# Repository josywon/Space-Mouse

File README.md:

# Space-Mouse
6DoF Space Mouse
Hardware folder holds CAD files and BOM of any hardware used
Electrical includes PCB and BOM of electrical materials
Firmware will be connecting the mouse to the software

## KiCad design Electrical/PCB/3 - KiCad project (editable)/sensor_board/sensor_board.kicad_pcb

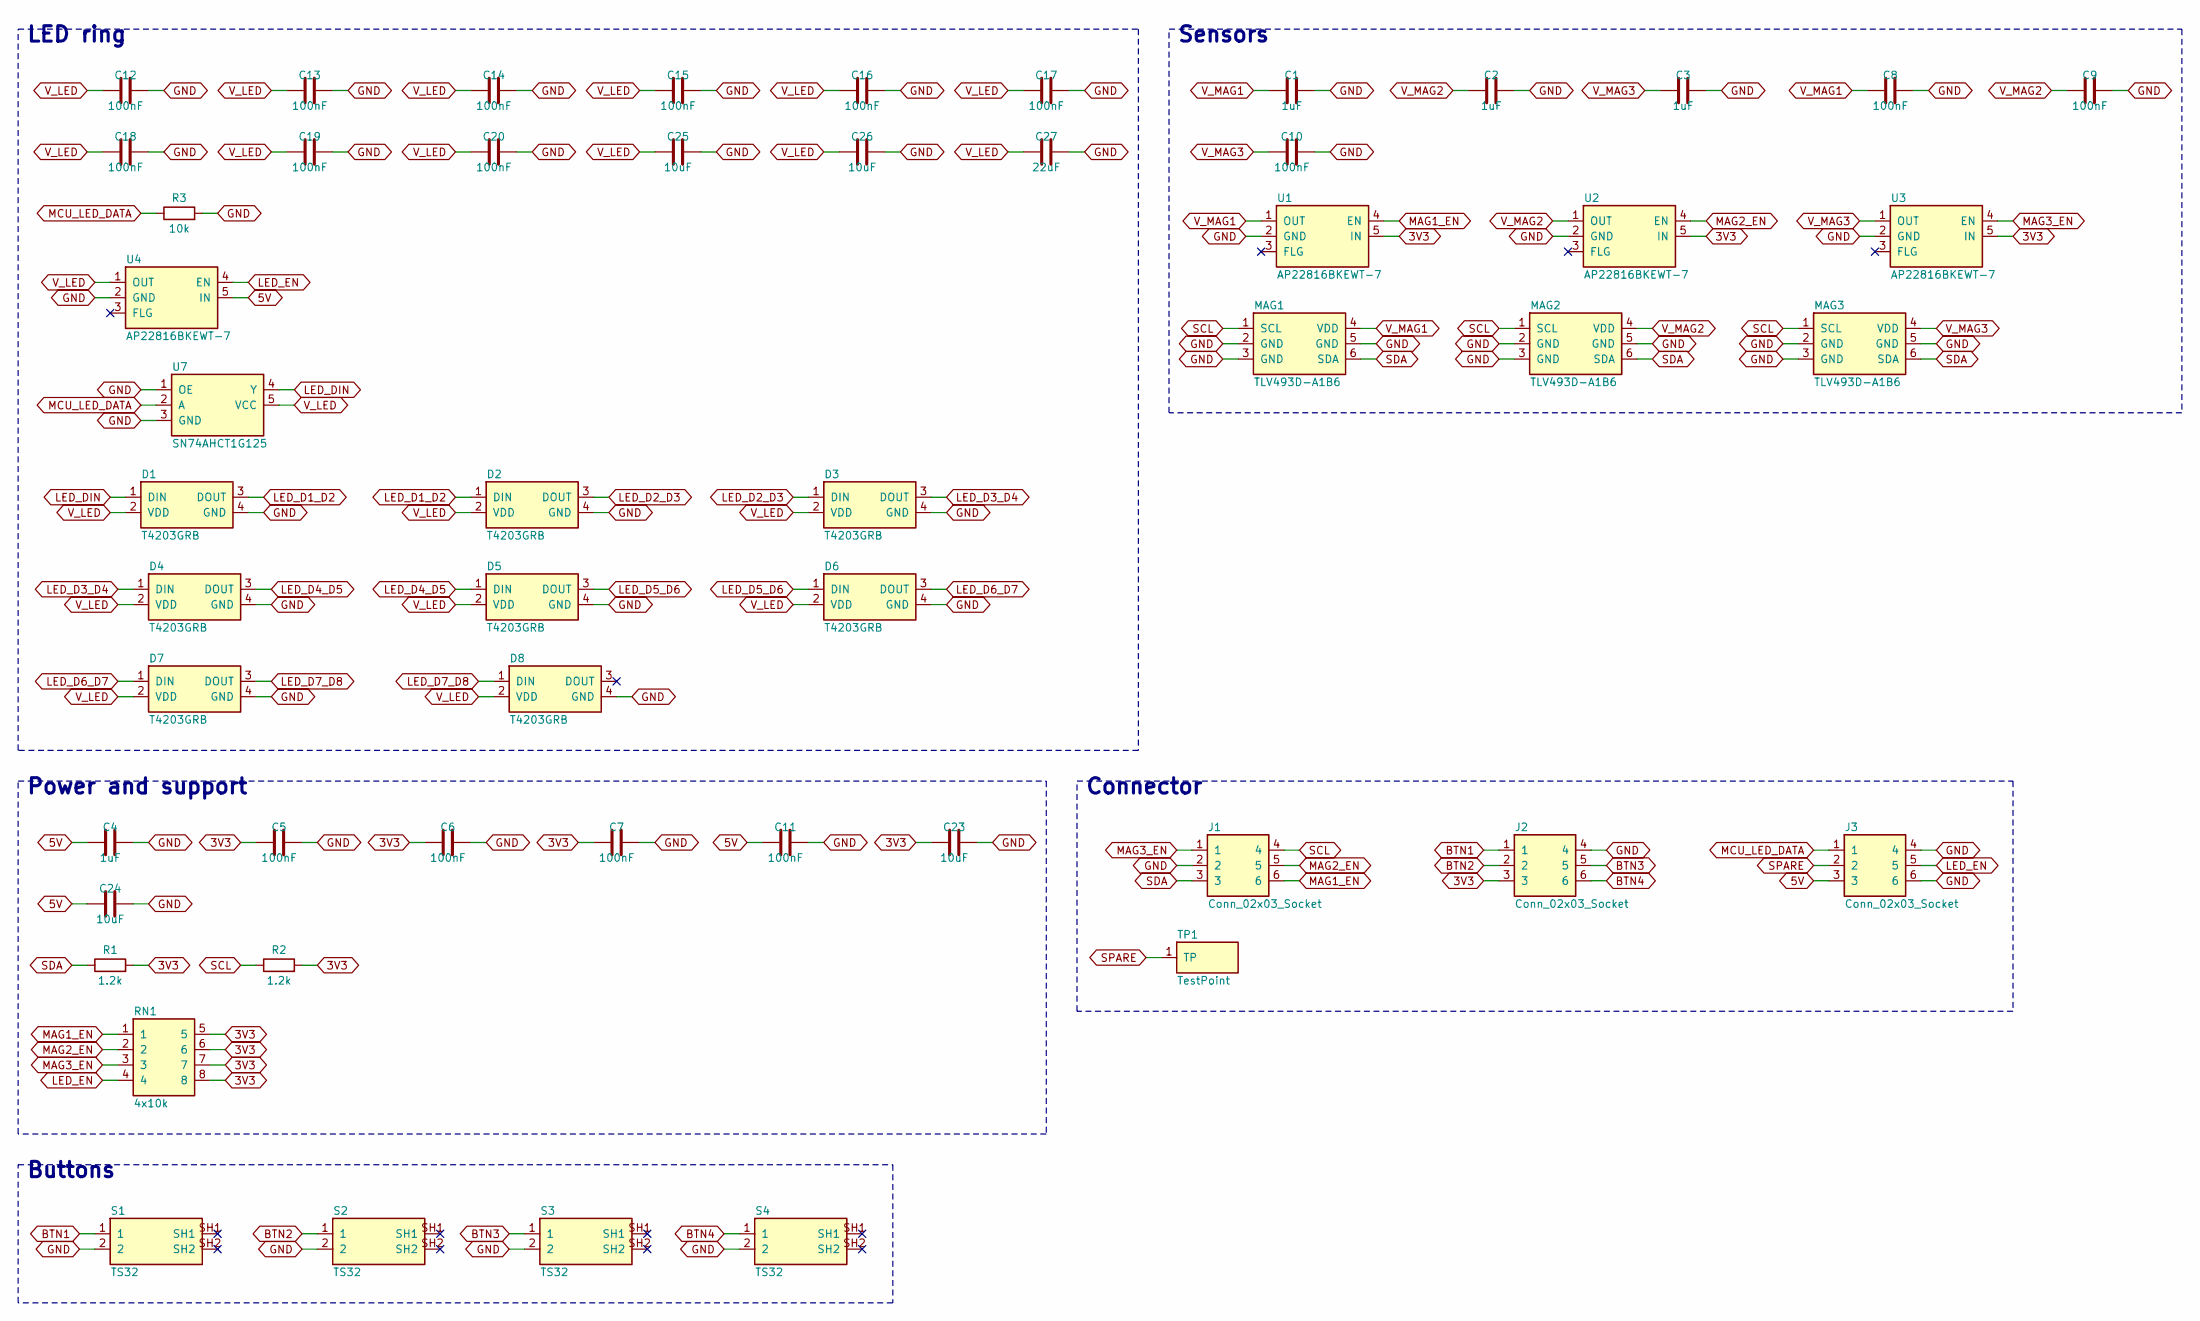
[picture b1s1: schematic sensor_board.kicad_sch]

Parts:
C1, C2, C3, C4: 1uF; C_1206_3216Metric
C5, C6, C7, C8, C9, C10, C11, C12, C13, C14, C15, C16, C17, C18, C19, C20: 100nF; C_0805_2012Metric
C23, C24, C25, C26: 10uF; C_0805_2012Metric
C27: 22uF; C_1206_3216Metric
D1, D2, D3, D4, D5, D6, D7, D8: T4203GRB; LED_T4203_SideView
J1, J2, J3: Conn_02x03_Socket; PinSocket_2x03_P2.00mm_Vertical
MAG1, MAG2, MAG3: TLV493D-A1B6; TSOP-6_1.65x3.05mm_P0.95mm
R1, R2: 1.2k; R_0805_2012Metric
R3: 10k; R_0805_2012Metric
RN1: 4x10k; R_Array_Convex_4x0603
S1, S2, S3, S4: TS32; SW_TS32_SideActuated
TP1: TestPoint; TestPoint_Pad_D1.5mm
U1, U2, U3, U4: AP22816BKEWT-7; TSOT-23-5
U7: SN74AHCT1G125; SOT-23-5

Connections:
3V3: C5.1, C6.1, C7.1, C23.1, J2.3, R1.2, R2.2, RN1.5, RN1.6, RN1.7, RN1.8, U1.5 (IN), U2.5 (IN), U3.5 (IN)
5V: C4.1, C11.1, C24.1, J3.3, U4.5 (IN)
BTN1: J2.1, S1.1
BTN2: J2.2, S2.1
BTN3: J2.5, S3.1
BTN4: J2.6, S4.1
GND: C1.2, C2.2, C3.2, C4.2, C5.2, C6.2, C7.2, C8.2, C9.2, C10.2, C11.2, C12.2, C13.2, C14.2, C15.2, C16.2, C17.2, C18.2, C19.2, C20.2, C23.2, C24.2, C25.2, C26.2, C27.2, D1.4 (GND), D2.4 (GND), D3.4 (GND), D4.4 (GND), D5.4 (GND), D6.4 (GND), D7.4 (GND), D8.4 (GND), J1.2, J2.4, J3.4, J3.6, MAG1.2 (GND), MAG1.3 (GND), MAG1.5 (GND), MAG2.2 (GND), MAG2.3 (GND), MAG2.5 (GND), MAG3.2 (GND), MAG3.3 (GND), MAG3.5 (GND), R3.2, S1.2, S2.2, S3.2, S4.2, U1.2 (GND), U2.2 (GND), U3.2 (GND), U4.2 (GND), U7.1 (OE), U7.3 (GND)
LED_D1_D2: D1.3 (DOUT), D2.1 (DIN)
LED_D2_D3: D2.3 (DOUT), D3.1 (DIN)
LED_D3_D4: D3.3 (DOUT), D4.1 (DIN)
LED_D4_D5: D4.3 (DOUT), D5.1 (DIN)
LED_D5_D6: D5.3 (DOUT), D6.1 (DIN)
LED_D6_D7: D6.3 (DOUT), D7.1 (DIN)
LED_D7_D8: D7.3 (DOUT), D8.1 (DIN)
LED_DIN: D1.1 (DIN), U7.4 (Y)
LED_EN: J3.5, RN1.4, U4.4 (EN)
MAG1_EN: J1.6, RN1.1, U1.4 (EN)
MAG2_EN: J1.5, RN1.2, U2.4 (EN)
MAG3_EN: J1.1, RN1.3, U3.4 (EN)
MCU_LED_DATA: J3.1, R3.1, U7.2 (A)
SCL: J1.4, MAG1.1 (SCL), MAG2.1 (SCL), MAG3.1 (SCL), R2.1
SDA: J1.3, MAG1.6 (SDA), MAG2.6 (SDA), MAG3.6 (SDA), R1.1
SPARE: J3.2, TP1.1
V_LED: C12.1, C13.1, C14.1, C15.1, C16.1, C17.1, C18.1, C19.1, C20.1, C25.1, C26.1, C27.1, D1.2 (VDD), D2.2 (VDD), D3.2 (VDD), D4.2 (VDD), D5.2 (VDD), D6.2 (VDD), D7.2 (VDD), D8.2 (VDD), U4.1 (OUT), U7.5 (VCC)
V_MAG1: C1.1, C8.1, MAG1.4 (VDD), U1.1 (OUT)
V_MAG2: C2.1, C9.1, MAG2.4 (VDD), U2.1 (OUT)
V_MAG3: C3.1, C10.1, MAG3.4 (VDD), U3.1 (OUT)

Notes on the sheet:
LED ring
Sensors
Power and support
Connector
Buttons

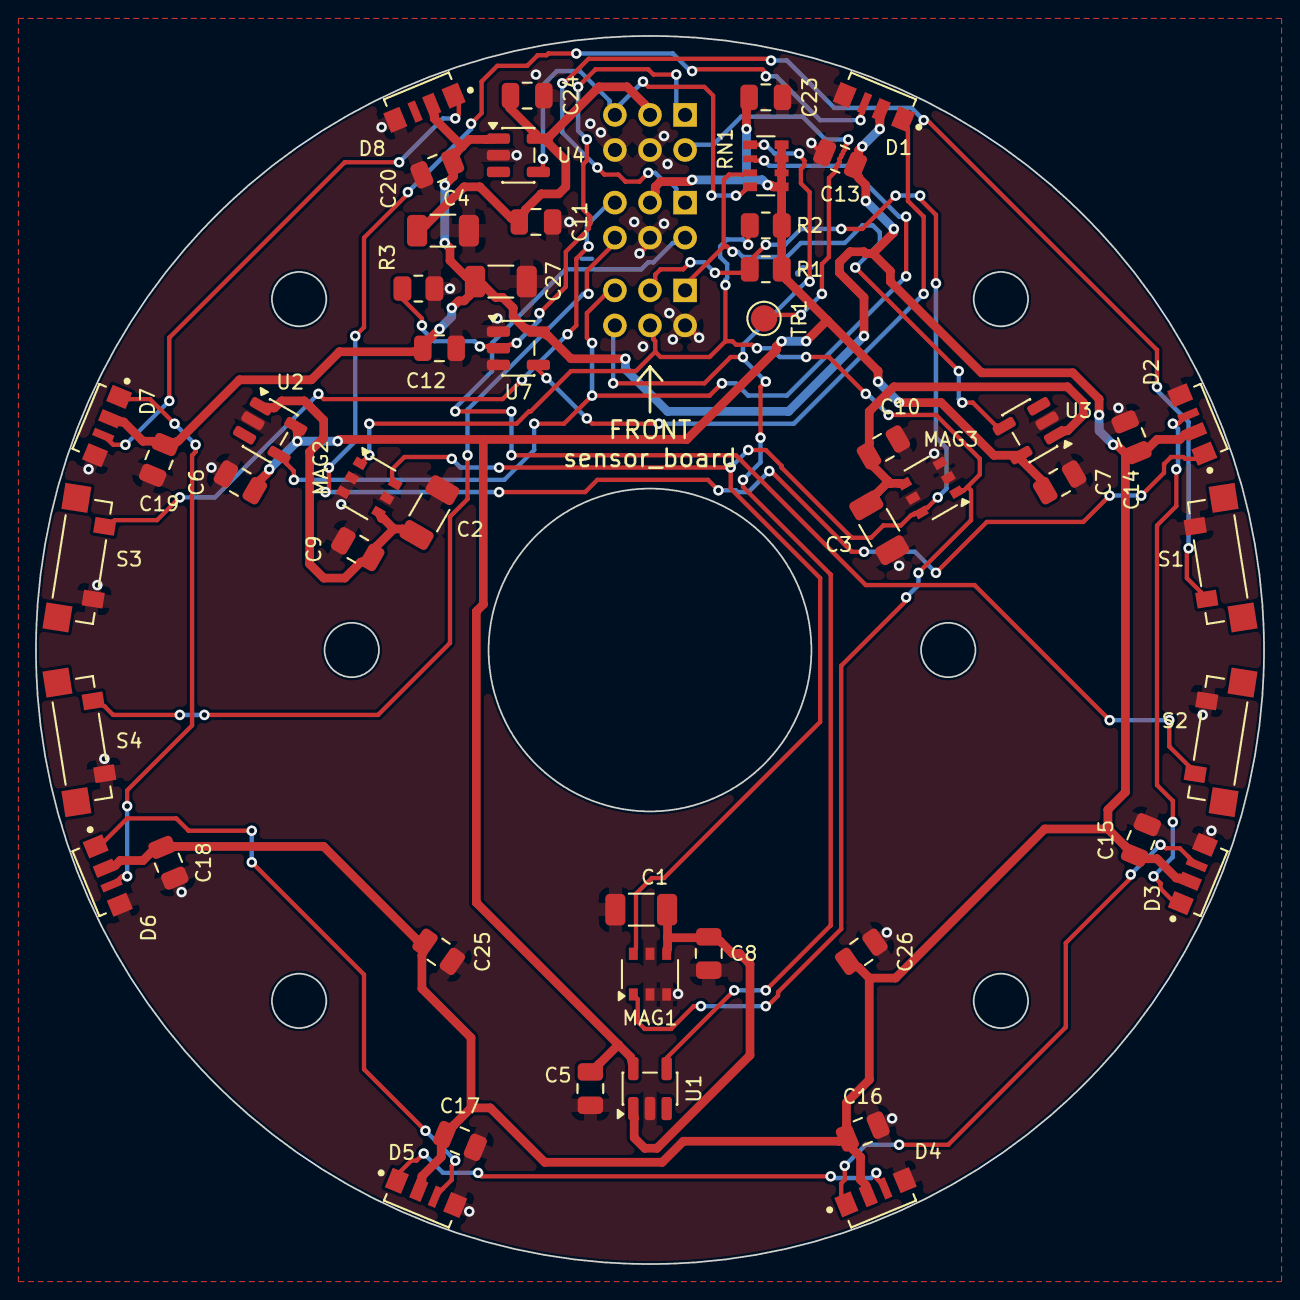
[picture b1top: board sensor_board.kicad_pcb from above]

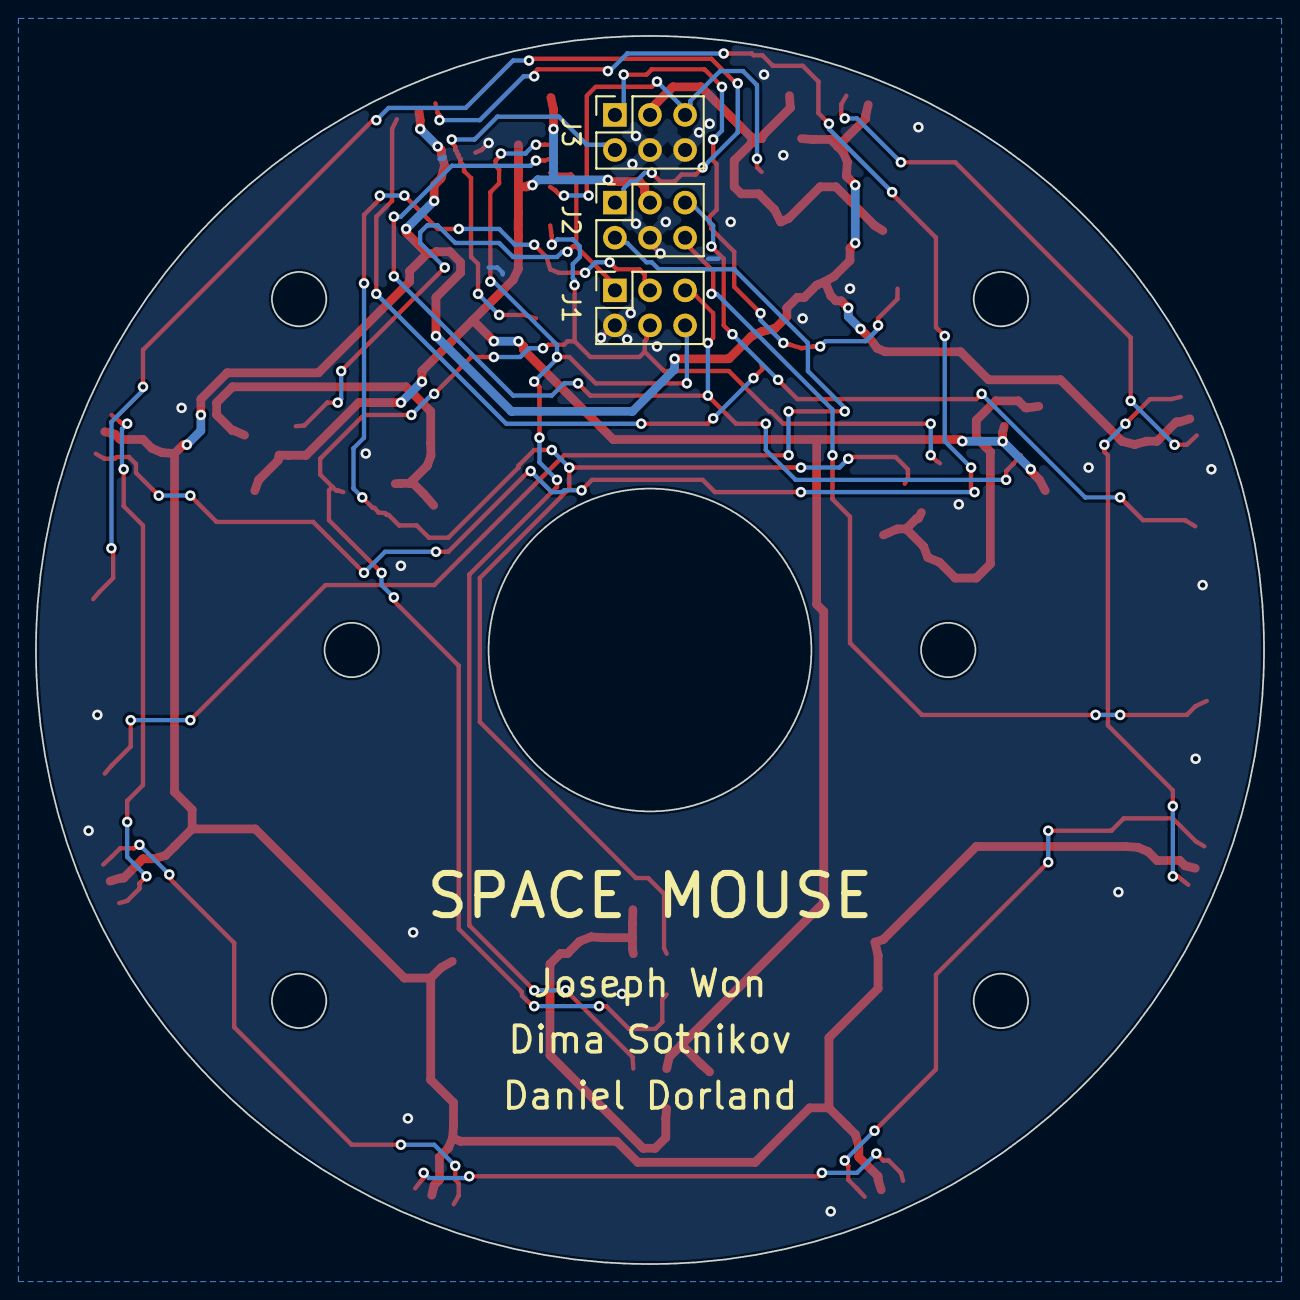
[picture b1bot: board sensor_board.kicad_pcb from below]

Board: 2 copper layers, 70.0 x 70.0 mm, 53 parts (3 on the bottom side), 27 nets.

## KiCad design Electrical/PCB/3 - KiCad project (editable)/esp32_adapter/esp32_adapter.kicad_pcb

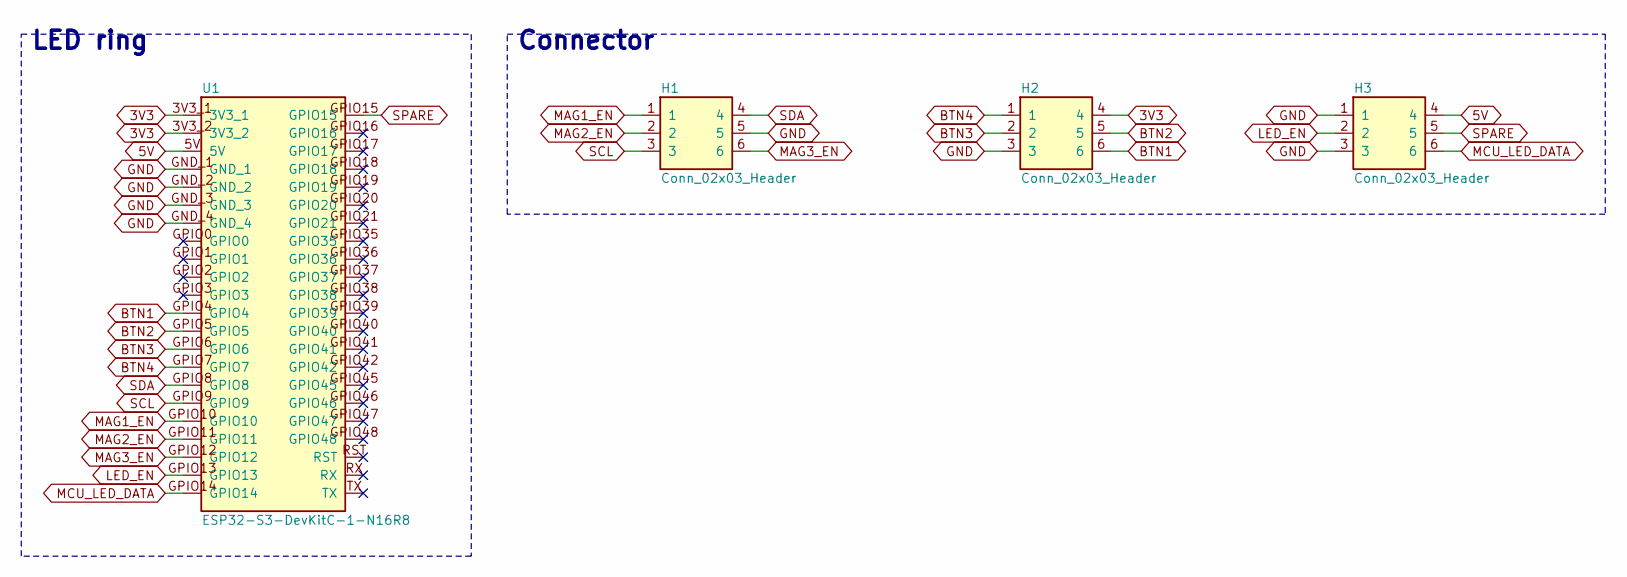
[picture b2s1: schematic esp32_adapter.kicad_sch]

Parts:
H1, H2, H3: Conn_02x03_Header; PinHeader_2x03_P2.00mm_Vertical
U1: ESP32-S3-DevKitC-1-N16R8; DevKit_ESP32S3_2x22_Flipped

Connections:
3V3: H2.4, U1.3V3_1, U1.3V3_2
5V: H3.4, U1.5V
BTN1: H2.6, U1.GPIO4
BTN2: H2.5, U1.GPIO5
BTN3: H2.2, U1.GPIO6
BTN4: H2.1, U1.GPIO7
GND: H1.5, H2.3, H3.1, H3.3, U1.GND_1, U1.GND_2, U1.GND_3, U1.GND_4
LED_EN: H3.2, U1.GPIO13
MAG1_EN: H1.1, U1.GPIO10
MAG2_EN: H1.2, U1.GPIO11
MAG3_EN: H1.6, U1.GPIO12
MCU_LED_DATA: H3.6, U1.GPIO14
SCL: H1.3, U1.GPIO9
SDA: H1.4, U1.GPIO8
SPARE: H3.5, U1.GPIO15

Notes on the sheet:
LED ring
Connector

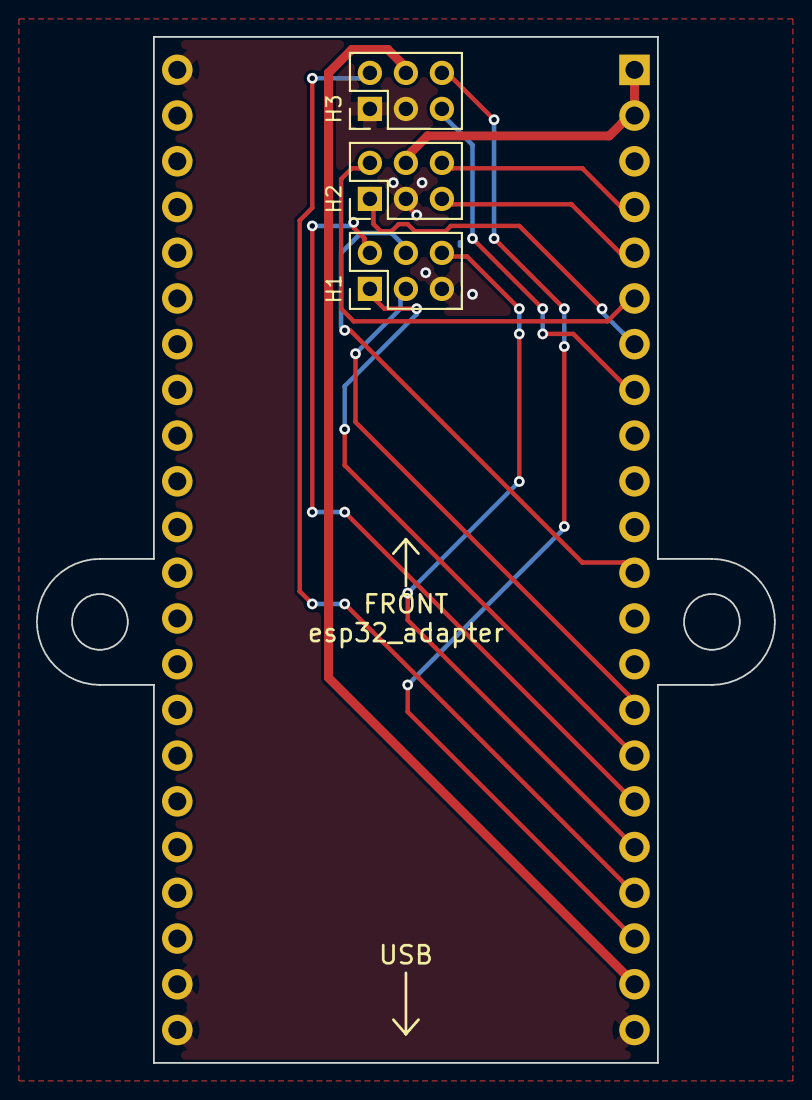
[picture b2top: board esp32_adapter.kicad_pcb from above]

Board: 2 copper layers, 41.0 x 57.0 mm, 4 parts (0 on the bottom side), 15 nets.
